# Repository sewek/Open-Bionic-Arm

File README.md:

# Open Bionic Arm
by Seweryn Malczewski

## Description
Open source project of automated bionic arm, created by me. It contains schematics of muscle activity detectors, motherboards with controllers, 3D models (and) designs of arm/hand construction and the software.

## Objectives of the project
Create a construction of the arm(with hand), needed electronic like the muscle sensors, controller and software that will be able to properly control the mechanism depending on the signals received from the muscles.

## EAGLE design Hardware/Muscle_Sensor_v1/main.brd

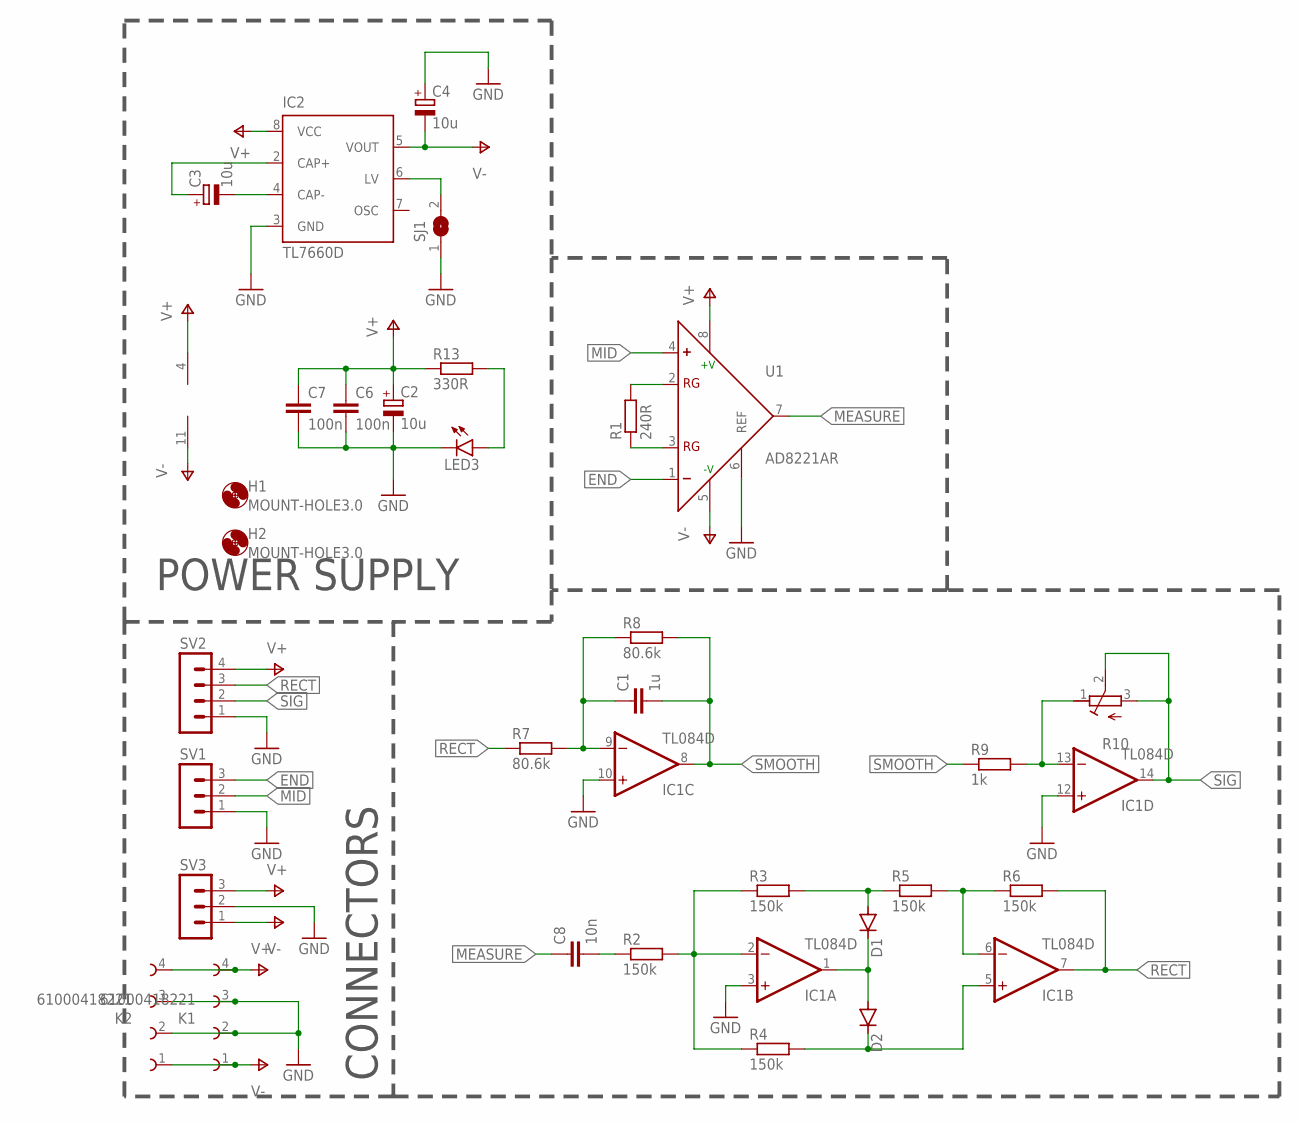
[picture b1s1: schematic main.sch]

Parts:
C1: 1u; C0805
C2, C3, C4: 10u; SMC_B
C6, C7: 100n; C0805
C8: 10n; C0805
D1, D2: DIODE-SOD80C; SOD80C
H1, H2: MOUNT-HOLE3.0; 3,0
IC1: TL084D; SO14
IC2: TL7660D; D_R-PDSO-G08
K1, K2: 61000418221
LED3: LEDCHIP-LED0805; CHIP-LED0805
R1: 240R; R1206
R2, R3, R4, R5, R6: 150k; R1206
R7, R8: 80.6k; R1206
R9: 1k; R1206
R10: R-TRIMM3314J; RTRIM3314J
R13: 330R; R1206
SJ1: SJ
SV1, SV3: MA03-1
SV2: MA04-1
U1: AD8221AR; SO8

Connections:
END: SV1.3, U1.1 (-)
GND: C2.-, C4.+, C6.2, C7.2, IC1.3 (+IN), IC1.10 (+IN), IC1.12 (+IN), IC2.3 (GND), K1.2, K1.3, K2.2, K2.3, LED3.C, SJ1.1, SV1.1, SV2.1, SV3.2, U1.6 (REF)
MEASURE: C8.1, U1.7 (OUT)
MID: SV1.2, U1.4 (+)
unnamed: IC1.2 (-IN), R2.2, R3.1, R4.1
unnamed: C8.2, R2.1
unnamed: D1.C, D2.A, IC1.1 (OUT)
unnamed: R1.2, U1.2 (RG)
unnamed: R1.1, U1.3 (RG)
unnamed: D1.A, R3.2, R5.1
unnamed: D2.C, IC1.5 (+IN), R4.2
unnamed: IC1.6 (-IN), R5.2, R6.1
unnamed: C1.1, IC1.9 (-IN), R7.2, R8.1
unnamed: IC2.6 (LV), SJ1.2
unnamed: IC1.13 (-IN), R9.2, R10.1 (E)
unnamed: C3.+, IC2.2 (CAP+)
unnamed: C3.-, IC2.4 (CAP-)
unnamed: LED3.A, R13.2
RECT: IC1.7 (OUT), R6.2, R7.1, SV2.3
SIG: IC1.14 (OUT), R10.2 (S), R10.3 (A), SV2.2
SMOOTH: C1.2, IC1.8 (OUT), R8.2, R9.1
V+: C2.+, C6.1, C7.1, IC1.4 (V+), IC2.8 (VCC), K1.4, K2.4, R13.1, SV2.4, SV3.3, U1.8 (+V)
V-: C4.-, IC1.11 (V-), IC2.5 (VOUT), K1.1, K2.1, SV3.1, U1.5 (-V)

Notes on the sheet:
POWER SUPPLY
CONNECTORS

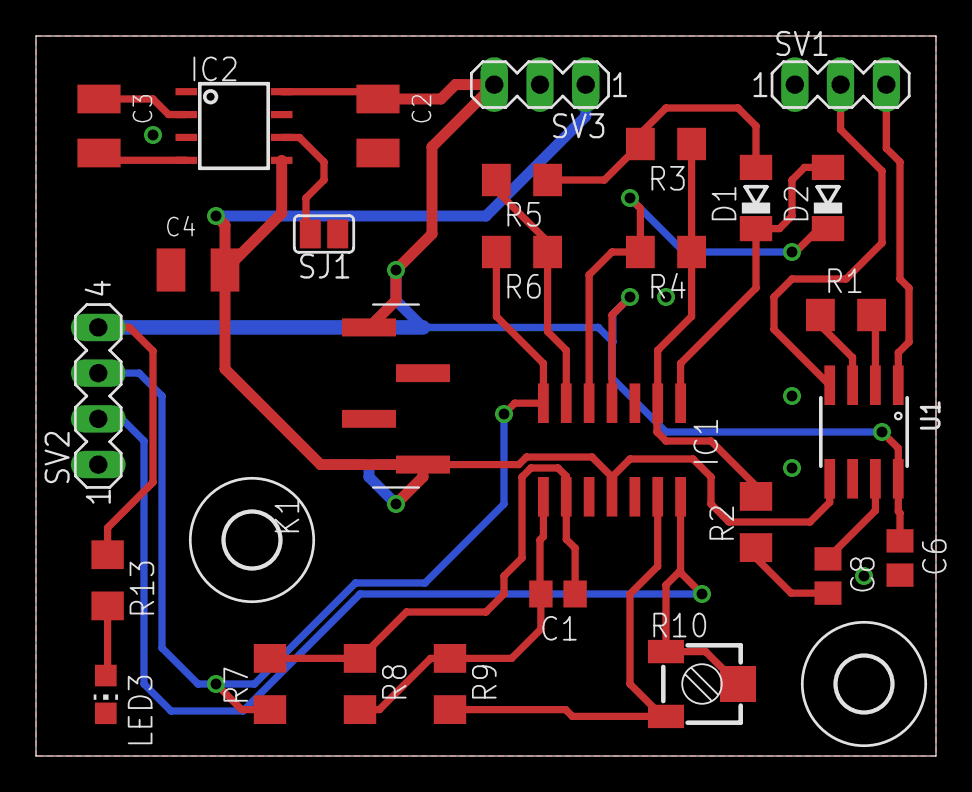
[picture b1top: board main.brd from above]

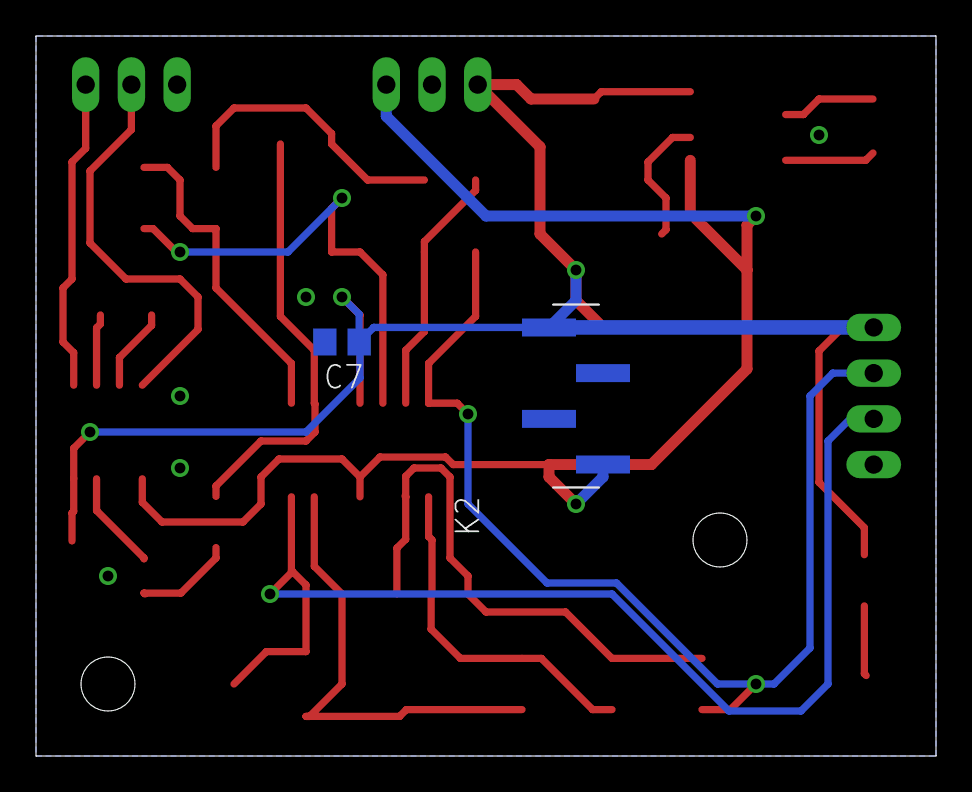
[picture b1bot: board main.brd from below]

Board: 2 copper layers, 50.0 x 40.0 mm, 32 parts (2 on the bottom side), 23 nets.

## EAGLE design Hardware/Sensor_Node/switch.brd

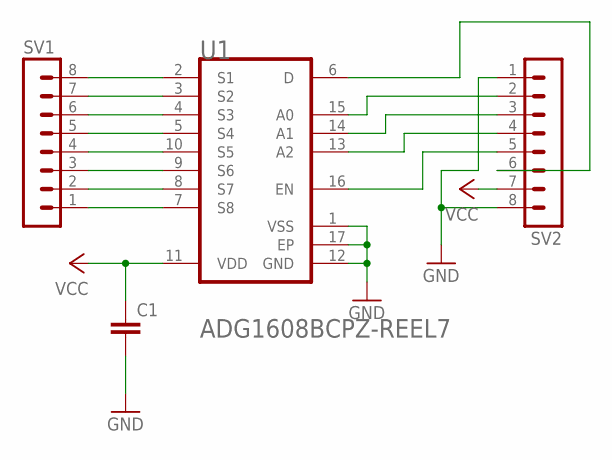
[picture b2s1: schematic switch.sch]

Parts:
C1: C-EUC0805; C0805
SV1, SV2: MA08-1
U1: ANALOG_DEVICES_ADG1608BCPZ-REEL7ANALOG_DEVICES_AD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; ANALOG_DEVICES_ADG1608BCPZ-REEL7_1

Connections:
GND: C1.2, SV2.1, SV2.8, U1.1 (VSS), U1.12 (GND), U1.17 (EP)
unnamed: SV2.5, U1.16 (EN)
unnamed: SV1.8, U1.2 (S1)
unnamed: SV2.6, U1.6 (D)
unnamed: SV2.2, U1.15 (A0)
unnamed: SV2.3, U1.14 (A1)
unnamed: SV2.4, U1.13 (A2)
unnamed: SV1.7, U1.3 (S2)
unnamed: SV1.6, U1.4 (S3)
unnamed: SV1.5, U1.5 (S4)
unnamed: SV1.4, U1.10 (S5)
unnamed: SV1.3, U1.9 (S6)
unnamed: SV1.2, U1.8 (S7)
unnamed: SV1.1, U1.7 (S8)
VCC: C1.1, SV2.7, U1.11 (VDD)

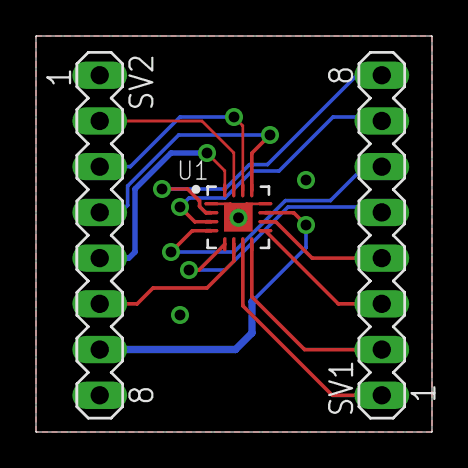
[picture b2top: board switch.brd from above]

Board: 2 copper layers, 22.0 x 22.0 mm, 4 parts (1 on the bottom side), 15 nets.

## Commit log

2019-04-10 Create Muscle_Sensor_v1 schematic
2019-04-11 Muscle_Sensor_v1 schematic fixes
2019-04-11 Create Muscle_Sensor_v1 board
2019-04-11 Set theme jekyll-theme-architect
2019-04-11 Init commit
2019-04-11 docs
2019-04-14 Software Init commit
2019-04-15 Move kernel-indev to another branch
2019-04-21 Software for arduino init
2019-04-21 Create some models
    It's first untested version, so I will probably have to make some fixes.
2019-05-27 Remove old files
2019-05-27 Added receive_data tool
2019-05-27 Add some models
2019-06-02 Create Arduino OpenBionicArmLite
2019-06-02 Create Muscle, Finger, Hand classes
2019-06-03 Update issue templates
2019-06-04 Update Hand, Finger, Muscle classes
2019-06-05 Update Muscle_Sensor_v1
2019-06-12 Update Arduino OpenBionicArmLite
2019-06-12 Update Tool make_sample
2019-06-12 Clean up
2019-08-19 Muscle Sensor Updates
    Schematic and board updates fixes some bugs of first version.
2019-08-19 Tools
2019-09-17 Create first models
2021-01-10 Some Changes
2021-03-11 Change esp files
2021-05-16 Create classification notepad
2021-05-16 Edit notepad
2021-05-16 Some changes in notepad
2021-06-06 Add hand models file with links

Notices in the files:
parts and their libraries:
Wurth_Elektronik_Electromechanic_Board_t: Copyright: Würth Elektronik
